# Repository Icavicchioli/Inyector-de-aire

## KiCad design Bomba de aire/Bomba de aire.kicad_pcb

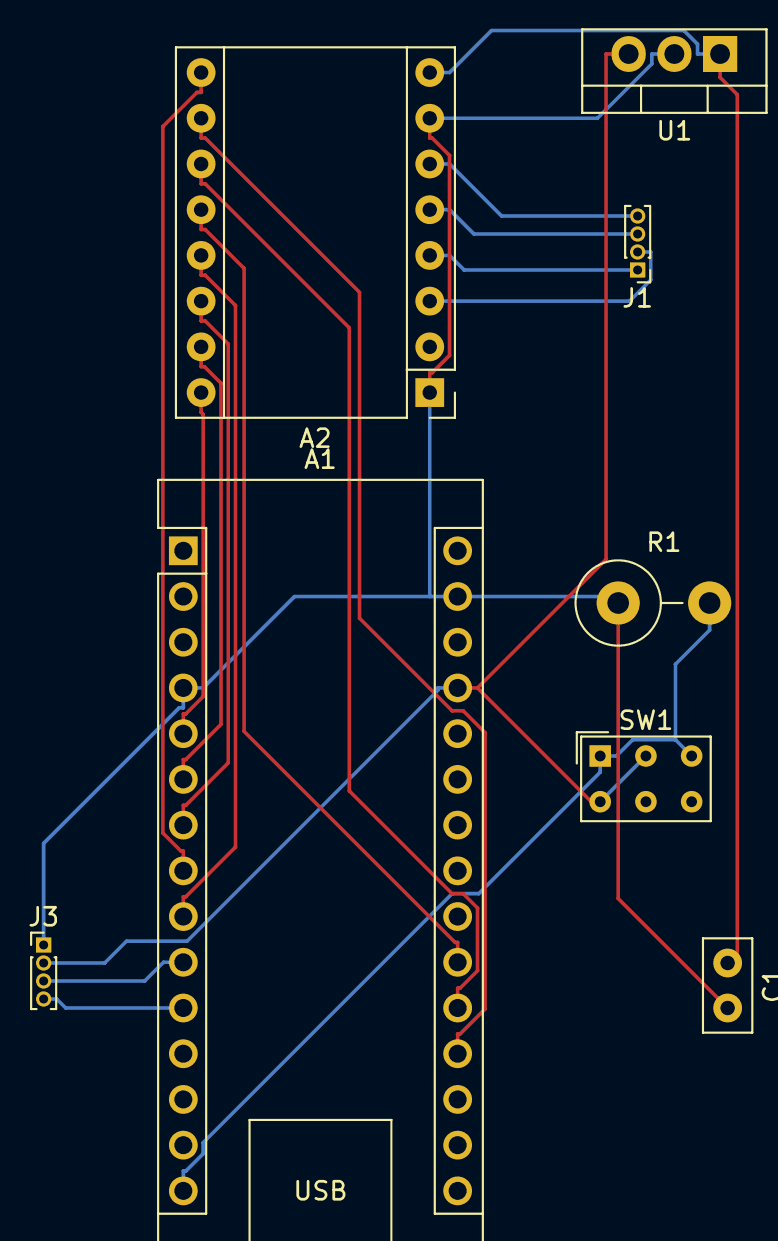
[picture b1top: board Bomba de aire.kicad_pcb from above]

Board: 2 copper layers, 8 parts (0 on the bottom side), 18 nets.

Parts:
A1: Arduino_Nano_v3.x; Arduino_Nano
A2: Pololu_Breakout_DRV8825; Pololu_Breakout-16_15.2x20.3mm
C1: 0.33 uF; C_Disc_D5.0mm_W2.5mm_P2.50mm
J1: Conn_01x04_Socket; PinHeader_1x04_P1.00mm_Vertical
J3: I2C socket; PinHeader_1x04_P1.00mm_Vertical
R1: 10 k; R_Axial_DIN0414_L11.9mm_D4.5mm_P5.08mm_Vertical
SW1: SW_Push_Dual; SW_NKK_GW12LJP
U1: LM7805_TO220; TO-220-3_Vertical

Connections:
!EN: A1.8 (D5), A2.9 (~EN)
!RST: A1.9 (D6), A2.13 (~RST)
!SLP: A1.7 (D4), A2.14 (~SLP)
+5V: A1.27 (+5V), J3.2, SW1.2, SW1.4, U1.3 (VO)
+12V: A2.8 (VMOT), C1.1, U1.1 (VI)
DIR: A1.5 (D2), A2.16 (DIR)
GND: A1.4 (GND), A1.29 (GND), A2.1 (GND), A2.7 (GND), C1.2, J3.1, R1.1, U1.2 (GND)
M0: A1.19 (A0), A2.10 (M0)
M1: A1.20 (A1), A2.11 (M1)
M2: A1.21 (A2), A2.12 (M2)
unnamed: A2.4 (A1), J1.1
unnamed: A2.3 (A2), J1.2
unnamed: A2.5 (B1), J1.3
unnamed: A2.6 (B2), J1.4
RUN: A1.15 (D12), R1.2, SW1.1, SW1.3
SCL: A1.11 (D8), J3.4
SDA: A1.10 (D7), J3.3
STEP: A1.6 (D3), A2.15 (STEP)

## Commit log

2024-07-13 esta cosa son los archivos de kicad
2024-07-14 header para el control del encoder (??)
    Crea una struct para el encoder que guarda los pines donde se conecyó y el ultimo estado conocido. Trae función para cargar los datos en la struct y una función que devuelve la dirección de giro, que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
2024-07-14 me faltó un struct y está la cosa que devuelve el estado del botón
2024-07-16 init: Creacion del proyecto con PlatformIO. Cambio nombres
2024-07-16 Cambio de nombre a bomba de aire
2024-07-17 Se separó header de .cpp y arreglos varios.
    Se se paró header de cpp y se arreglaron definciones y cosas que estaban mal. Se probó que compile en compilador online.
2024-07-17 Update encoder.cpp
    Andaba todo para el ogt, ahora está probado en arduino fisico
    Lo unico el encoder medio que avanza de a 2, no 1, eso hay que considerar, es tema mecánico, no electrónico
2024-07-17 Update encoder.cpp
    Un espacio y me comí una c en corrección.
2024-07-23 nueva lib para stepper
2024-07-24 clase stepper
2024-07-24 stepper
2024-07-24 stepper_driver
2024-07-24 stapper
2024-07-24 compila
2024-08-06 encoder trabaja con punteros
2024-08-06 arreglar stepper
2024-08-06 fixed stepper again
2024-08-06 caca
2024-08-06 Optimizacion de get_encoder_direction
2024-08-06 factor correccion mecanica encoder
2024-08-08 Encoder migrado de C a C++
2024-08-09 READMEs creados
2024-08-10 clase para parametros de maquina
2024-08-10 funciona en proteus con la lib de eeprom castrada en algo de strings, no deberia hacer problema en arduino
2024-08-11 menu probado proteus
2024-08-11 main del proteus funcando con stepper, encoder y menu
